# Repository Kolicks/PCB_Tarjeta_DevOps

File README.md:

# ⚙️ PCB_Tarjeta_DevOps
**Generic Development Console with Ethernet and USB Connectivity**

---

<p align="center">
  
</p>

---

## 📘 Overview
**PCB_Tarjeta_DevOps** is a versatile, custom-designed console PCB created primarily as a **personal exercise in complex two-layer design and Ethernet integration**.  
It serves as a **general-purpose development board** adapted from the **ST Nucleo-F412ZG** design, focusing on practical layout challenges and signal-integrity learning (Ethernet, differential pairs, impedance control).

<p align="center">

  <br>
  <em>3D renders of the PCB_Tarjeta_DevOps — Top and Bottom views</em>
</p>

---

## ⚙️ General Information
- A **general-purpose console**, not intended for a specific application.  
- Designed as a **learning exercise**, implementing many components on only **two layers** to increase design difficulty.  
- Served as an **introduction to Ethernet PCB layout**, including **differential pair routing** and **impedance control**.  
- Several schematic blocks were **adapted from the ST Nucleo-F412ZG** for familiarity and reference.  

<p align="center">
  
  <br>
  <em>Full schematic diagram of the PCB_Tarjeta_DevOps (KiCad 9)</em>
</p>

---

## 🔧 Characteristics
- Acts as a **multi-purpose development console**.  
- Supports **USB power and programming**.  
- Integrates **Ethernet connectivity** with differential pair routing and impedance matching.  
- Includes **8 Inputs and 8 Outputs**:  
  - **Outputs for industrial/power use** driven by **ITS4090QEPDXUMA1** — up to **1.5 A** each, suitable for **24 V industrial control**.  
  - **8 isolated outputs** using **TLP290-4** optocouplers (potential-free, up to 24 V).  
- Features a **hardware switch selector** to toggle between **programming** and **debugging** modes.  
- Includes a **real-time clock (RTC)** with **CR2032 battery backup**.  
- Provides **five tactile buttons** for user interaction with the display or user interface.  

<p align="center">
  
  <br>
  <em>Top layer routing and overall PCB layout (KiCad 9)</em>
</p>

---

## ⚠️ Design Notes
- **Display Section:**  
  - Multiple components in the display area require mechanical supports and connectors.  
  - Some footprints should be marked as **DNP (Do Not Populate)** and clearly specified for **DFM/DFA** purposes.  
- **Ethernet Interface:**  
  - Differential pairs are **impedance-matched to 100 Ω**, validated using **JLCPCB’s impedance calculator** and fabrication stack-up data.  
  - **USB traces** are not impedance-controlled in this revision (planned improvement).  
- **DFM Analysis (JLCPCB DFM tool):**  
  - Found **drilling overlaps** in display-related holes (mechanical supports and signals).  
  - **USB-C footprint issue:** plated hole size **0.60 mm, required >0.61 mm** tolerance.  
- **Silkscreen and Drill Issues:**  
  - Some silkscreen elements **collide with through holes** but remain legible.  
  - **Line width warnings** flagged for narrow silkscreen traces — minor fabrication risk, acceptable in prototype runs.  
- Overall design remains **manufacturable** and **functionally valid**, despite minor DFM flags.  

---

## 🧩 Repository Structure
PCB_Tarjeta_DevOps/

├── schematic/ # KiCad schematic files

├── pcb_layout/ # KiCad PCB layout files

├── gerbers/ # Gerber fabrication files

├── images/ # Rendered visuals (3D, SCH, PCB)

├── LICENSE # Hardware license (CERN-OHL-P v2.0)

└── README.md # Project documentation

---

## 📜 License
This hardware design is released under the **CERN Open Hardware License v2 – Permissive (CERN-OHL-P-2.0)**.  
You are free to use, modify, and distribute this design, provided that:
- The license is included with redistributions.
- Proper credit is given to the original author.

More info: https://cern-ohl.web.cern.ch/

---

## 👤 Author
**Project:** PCB_Tarjeta_DevOps  
**Author:** [Kolicks]  
**Toolchain:** KiCad 9  
**Version:** 9.0  

---

## 🧱 Future Improvements
- Redesign **USB differential pair** routing with impedance control.  
- Correct **DFM-related drilling and silkscreen** warnings.  
- Mark **DNP parts** for display connectors and update BOM.

---

⭐ *If you find this project useful or educational, please consider starring the repository and sharing feedback!*

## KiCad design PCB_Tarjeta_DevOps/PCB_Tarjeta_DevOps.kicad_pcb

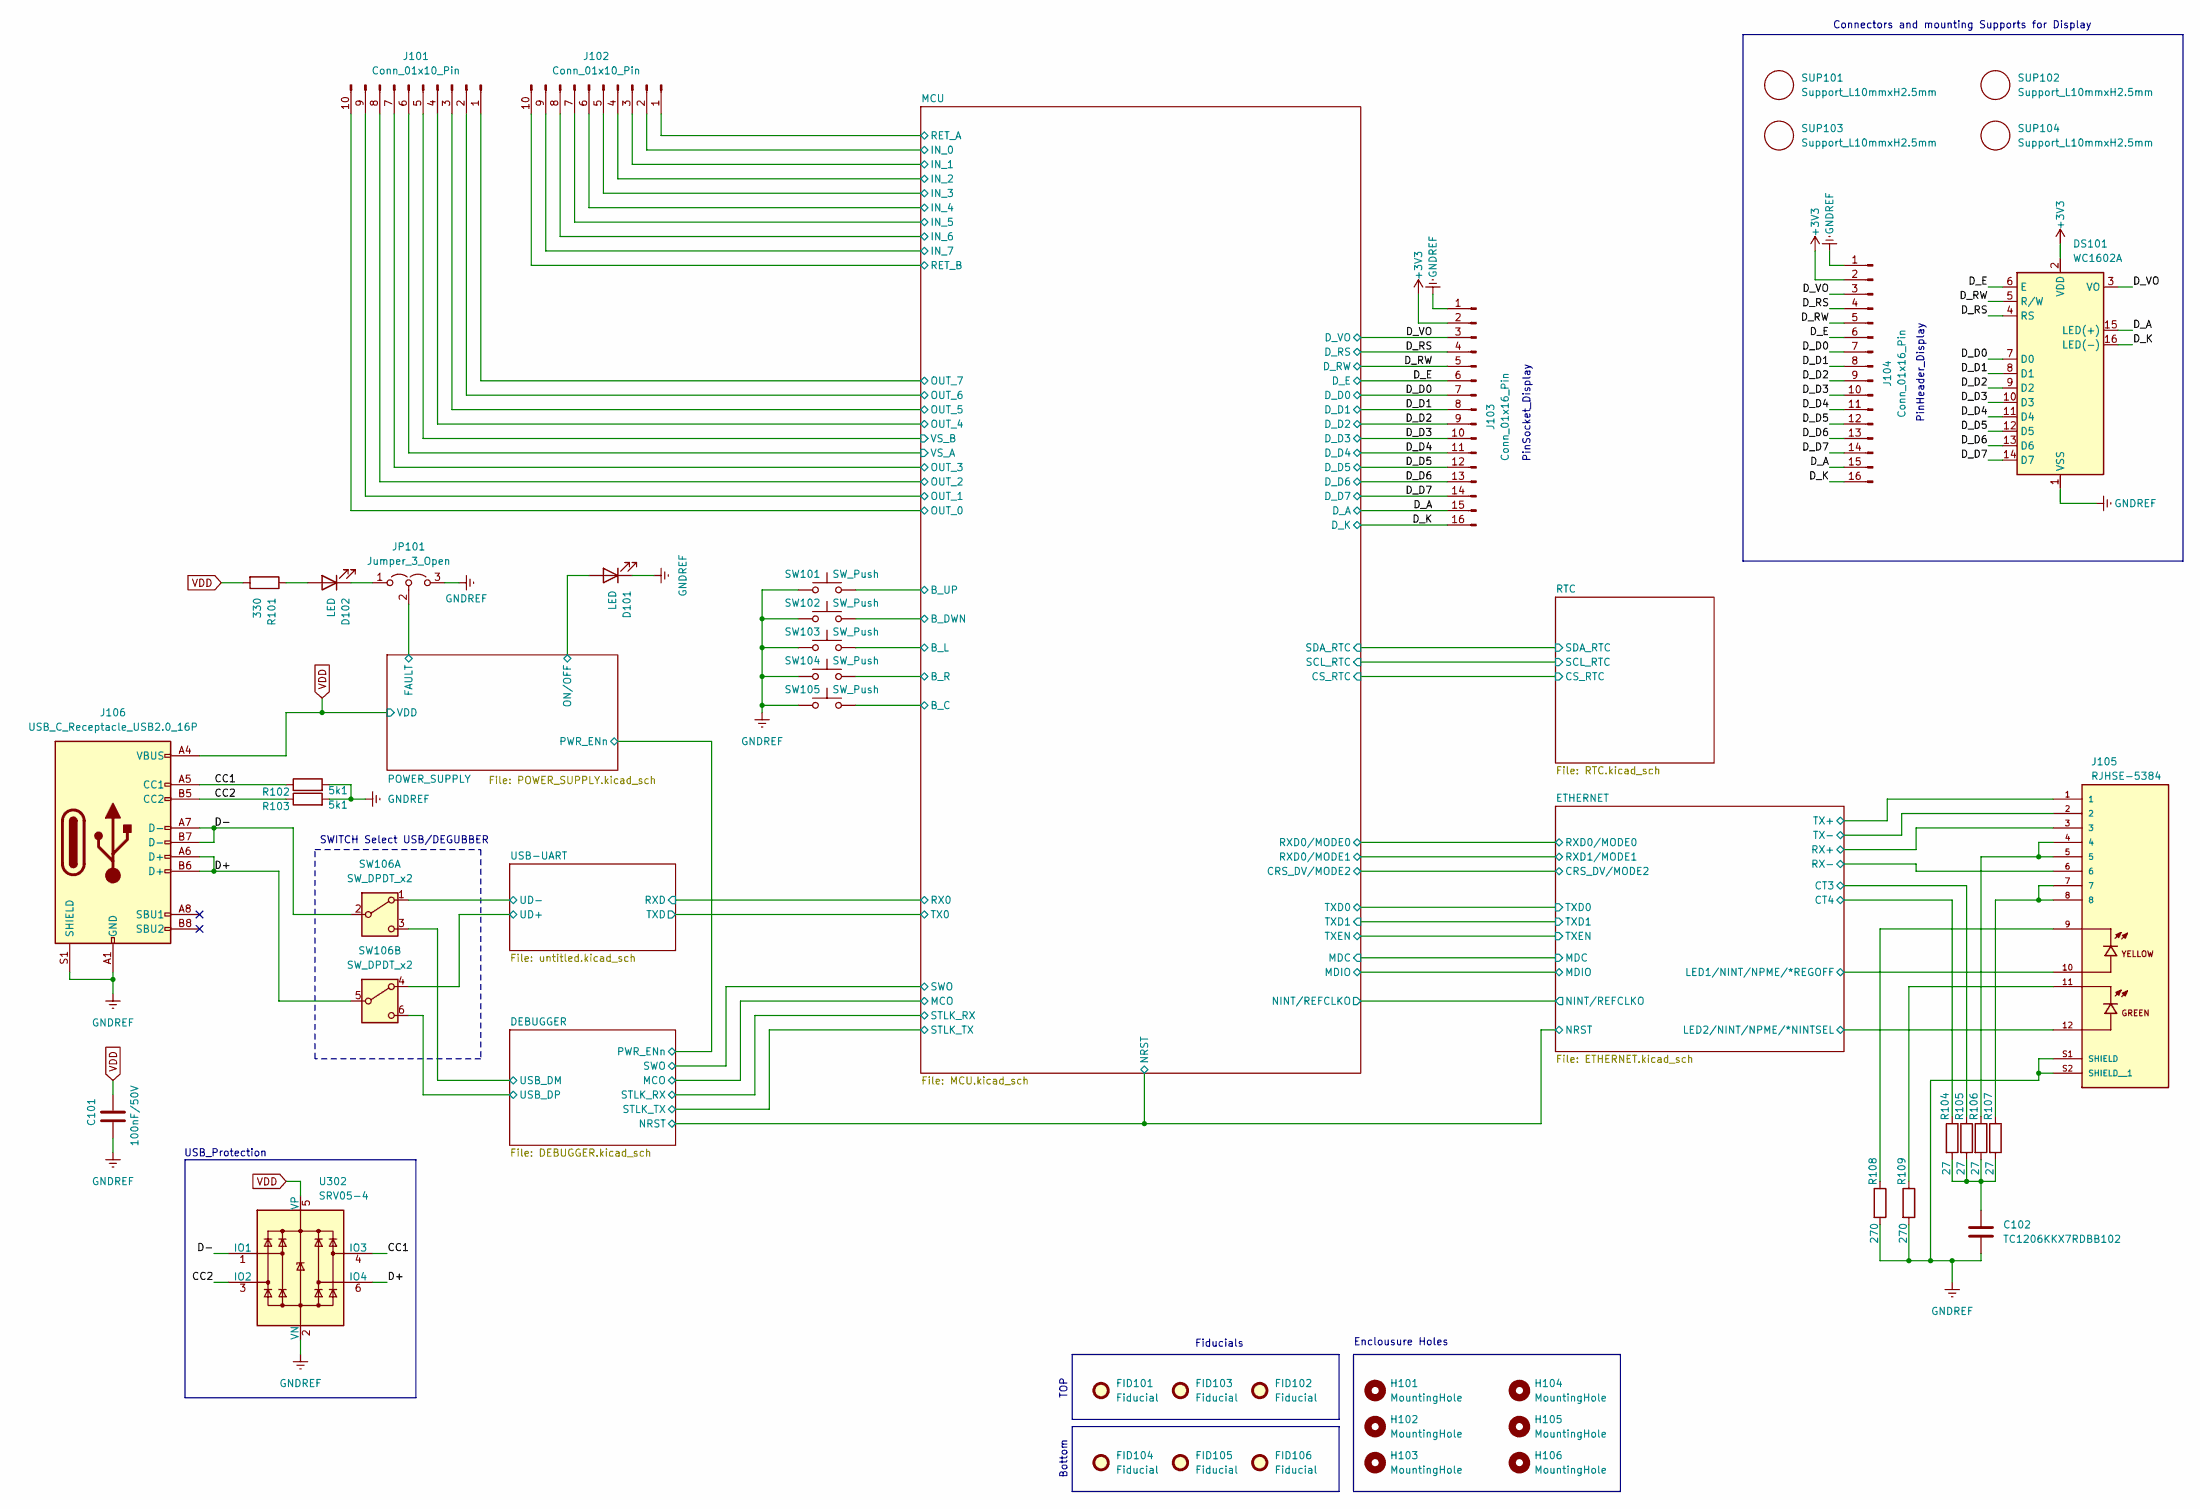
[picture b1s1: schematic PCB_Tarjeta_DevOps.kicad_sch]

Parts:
C101: 100nF/50V; C_0603_1608Metric_Pad1.08x0.95mm_HandSolder
C102: TC1206KKX7RDBB102; C_0603_1608Metric_Pad1.08x0.95mm_HandSolder
D101, D102: LED; LED_0201_0603Metric_Pad0.64x0.40mm_HandSolder
DS101: WC1602A
FID101, FID102, FID103, FID104, FID105, FID106: Fiducial; Fiducial_1.5mm_Mask3mm
H101, H102, H103, H104, H105, H106: MountingHole; MountingHole_3.2mm_M3_ISO14580
J101, J102: Conn_01x10_Pin; TerminalBlock_Phoenix_MPT-0,5-10-2.54_1x10_P2.54mm_Horizont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
J103: Conn_01x16_Pin; PinSocket_1x16_P2.54mm_Vertical
J104: Conn_01x16_Pin; PinHeader_1x16_P2.54mm_Vertical
J105: RJHSE-5384; AMPHENOL_RJHSE-5384; PARTREV E
J106: USB_C_Receptacle_USB2.0_16P; USB_C_Receptacle_Palconn_UTC16-G
JP101: Jumper_3_Open; PinHeader_1x03_P2.54mm_Vertical
R101: 330; R_0603_1608Metric_Pad0.98x0.95mm_HandSolder
R102, R103: 5k1; R_0603_1608Metric_Pad0.98x0.95mm_HandSolder
R104, R105, R106, R107: 27; R_0603_1608Metric_Pad0.98x0.95mm_HandSolder
R108, R109: 270; R_0603_1608Metric_Pad0.98x0.95mm_HandSolder
SUP101, SUP102, SUP103, SUP104: Support_L10mmxH2.5mm; Support_1x01_L1.0mmxH2.5mm_Vertical
SW101, SW102, SW103, SW104, SW105: SW_Push; SW_PUSH_6mm_H13mm
SW106: SW_DPDT_x2; SW_CK_JS202011CQN_DPDT_Straight
U302: SRV05-4; SOT-23-6

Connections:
+3V3: DS101.2 (VDD), J103.2, J104.2; also elsewhere on the board
/CC1: J106.A5 (CC1), R102.1, U302.4 (IO3)
/CC2: J106.B5 (CC2), R103.1, U302.3 (IO2)
/D+: J106.A6 (D+), J106.B6 (D+), SW106.5 (B), U302.6 (IO4)
/D-: J106.A7 (D-), J106.B7 (D-), SW106.2 (B), U302.1 (IO1)
/DEBUGGER/USB_DM: SW106.3 (C); also elsewhere on the board
/DEBUGGER/USB_DP: SW106.6 (C); also elsewhere on the board
/D_A: DS101.15 (LED(+)), J103.15, J104.15; also elsewhere on the board
/D_D0: DS101.7 (D0), J103.7, J104.7; also elsewhere on the board
/D_D1: DS101.8 (D1), J103.8, J104.8; also elsewhere on the board
/D_D2: DS101.9 (D2), J103.9, J104.9; also elsewhere on the board
/D_D3: DS101.10 (D3), J103.10, J104.10; also elsewhere on the board
/D_D4: DS101.11 (D4), J103.11, J104.11; also elsewhere on the board
/D_D5: DS101.12 (D5), J103.12, J104.12; also elsewhere on the board
/D_D6: DS101.13 (D6), J103.13, J104.13; also elsewhere on the board
/D_D7: DS101.14 (D7), J103.14, J104.14; also elsewhere on the board
/D_E: DS101.6 (E), J103.6, J104.6; also elsewhere on the board
/D_K: DS101.16 (LED(-)), J103.16, J104.16; also elsewhere on the board
/D_RS: DS101.4 (RS), J103.4, J104.4; also elsewhere on the board
/D_RW: DS101.5 (R/W), J103.5, J104.5; also elsewhere on the board
/D_VO: DS101.3 (VO), J103.3, J104.3; also elsewhere on the board
/ETHERNET/CT3: R105.1; also elsewhere on the board
/ETHERNET/CT4: R104.1; also elsewhere on the board
/ETHERNET/LED1/NINT/NPME/*REGOFF: J105.10; also elsewhere on the board
/ETHERNET/LED2/NINT/NPME/*NINTSEL: J105.12; also elsewhere on the board
/ETHERNET/RX+: J105.3; also elsewhere on the board
/ETHERNET/RX-: J105.6; also elsewhere on the board
/ETHERNET/TX+: J105.1; also elsewhere on the board
/ETHERNET/TX-: J105.2; also elsewhere on the board
/MCU/B_C: SW105.2; also elsewhere on the board
/MCU/B_DWN: SW102.2; also elsewhere on the board
/MCU/B_L: SW103.2; also elsewhere on the board
/MCU/B_R: SW104.2; also elsewhere on the board
/MCU/B_UP: SW101.2; also elsewhere on the board
/MCU/IN_0: J102.2; also elsewhere on the board
/MCU/IN_1: J102.3; also elsewhere on the board
/MCU/IN_2: J102.4; also elsewhere on the board
/MCU/IN_3: J102.5; also elsewhere on the board
/MCU/IN_4: J102.6; also elsewhere on the board
/MCU/IN_5: J102.7; also elsewhere on the board
/MCU/IN_6: J102.8; also elsewhere on the board
/MCU/IN_7: J102.9; also elsewhere on the board
/MCU/OUT_0: J101.10; also elsewhere on the board
/MCU/OUT_1: J101.9; also elsewhere on the board
/MCU/OUT_2: J101.8; also elsewhere on the board
/MCU/OUT_3: J101.7; also elsewhere on the board
/MCU/OUT_4: J101.4; also elsewhere on the board
/MCU/OUT_5: J101.3; also elsewhere on the board
/MCU/OUT_6: J101.2; also elsewhere on the board
/MCU/OUT_7: J101.1; also elsewhere on the board
/MCU/RET_A: J102.1; also elsewhere on the board
/MCU/RET_B: J102.10; also elsewhere on the board
/MCU/VS_A: J101.6; also elsewhere on the board
/MCU/VS_B: J101.5; also elsewhere on the board
/POWER_SUPPLY/FAULT: JP101.2 (C); also elsewhere on the board
/POWER_SUPPLY/ON/OFF: D101.2 (A); also elsewhere on the board
/USB-UART/UD+: SW106.4 (A); also elsewhere on the board
/USB-UART/UD-: SW106.1 (A); also elsewhere on the board
GNDREF: C101.2, C102.2, D101.1 (K), DS101.1 (VSS), J103.1, J104.1, J105.S1 (SHIELD), J105.S2 (SHIELD__1), J106.A1 (GND), J106.A12 (GND), J106.B1 (GND), J106.B12 (GND), J106.S1 (SHIELD), JP101.3 (B), R102.2, R103.2, R108.2, R109.2, SW101.1, SW102.1, SW103.1, SW104.1, SW105.1, U302.2 (VN); also elsewhere on the board
unnamed: C102.1, R104.2, R105.2, R106.2, R107.2
unnamed: D102.2 (A), R101.1
unnamed: D102.1 (K), JP101.1 (A)
unnamed: J105.4, J105.5, R106.1
unnamed: J105.7, J105.8, R107.1
unnamed: J105.9, R108.1
unnamed: J105.11, R109.1
VDD: C101.1, J106.A4 (VBUS), J106.A9 (VBUS), J106.B4 (VBUS), J106.B9 (VBUS), R101.2, U302.5 (VP); also elsewhere on the board

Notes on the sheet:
Bottom
PinHeader_Display
Connectors and mounting Supports for Display
USB_Protection
Enclousure Holes
Fiducials
SWITCH Select USB/DEGUBBER
TOP
PinSocket_Display

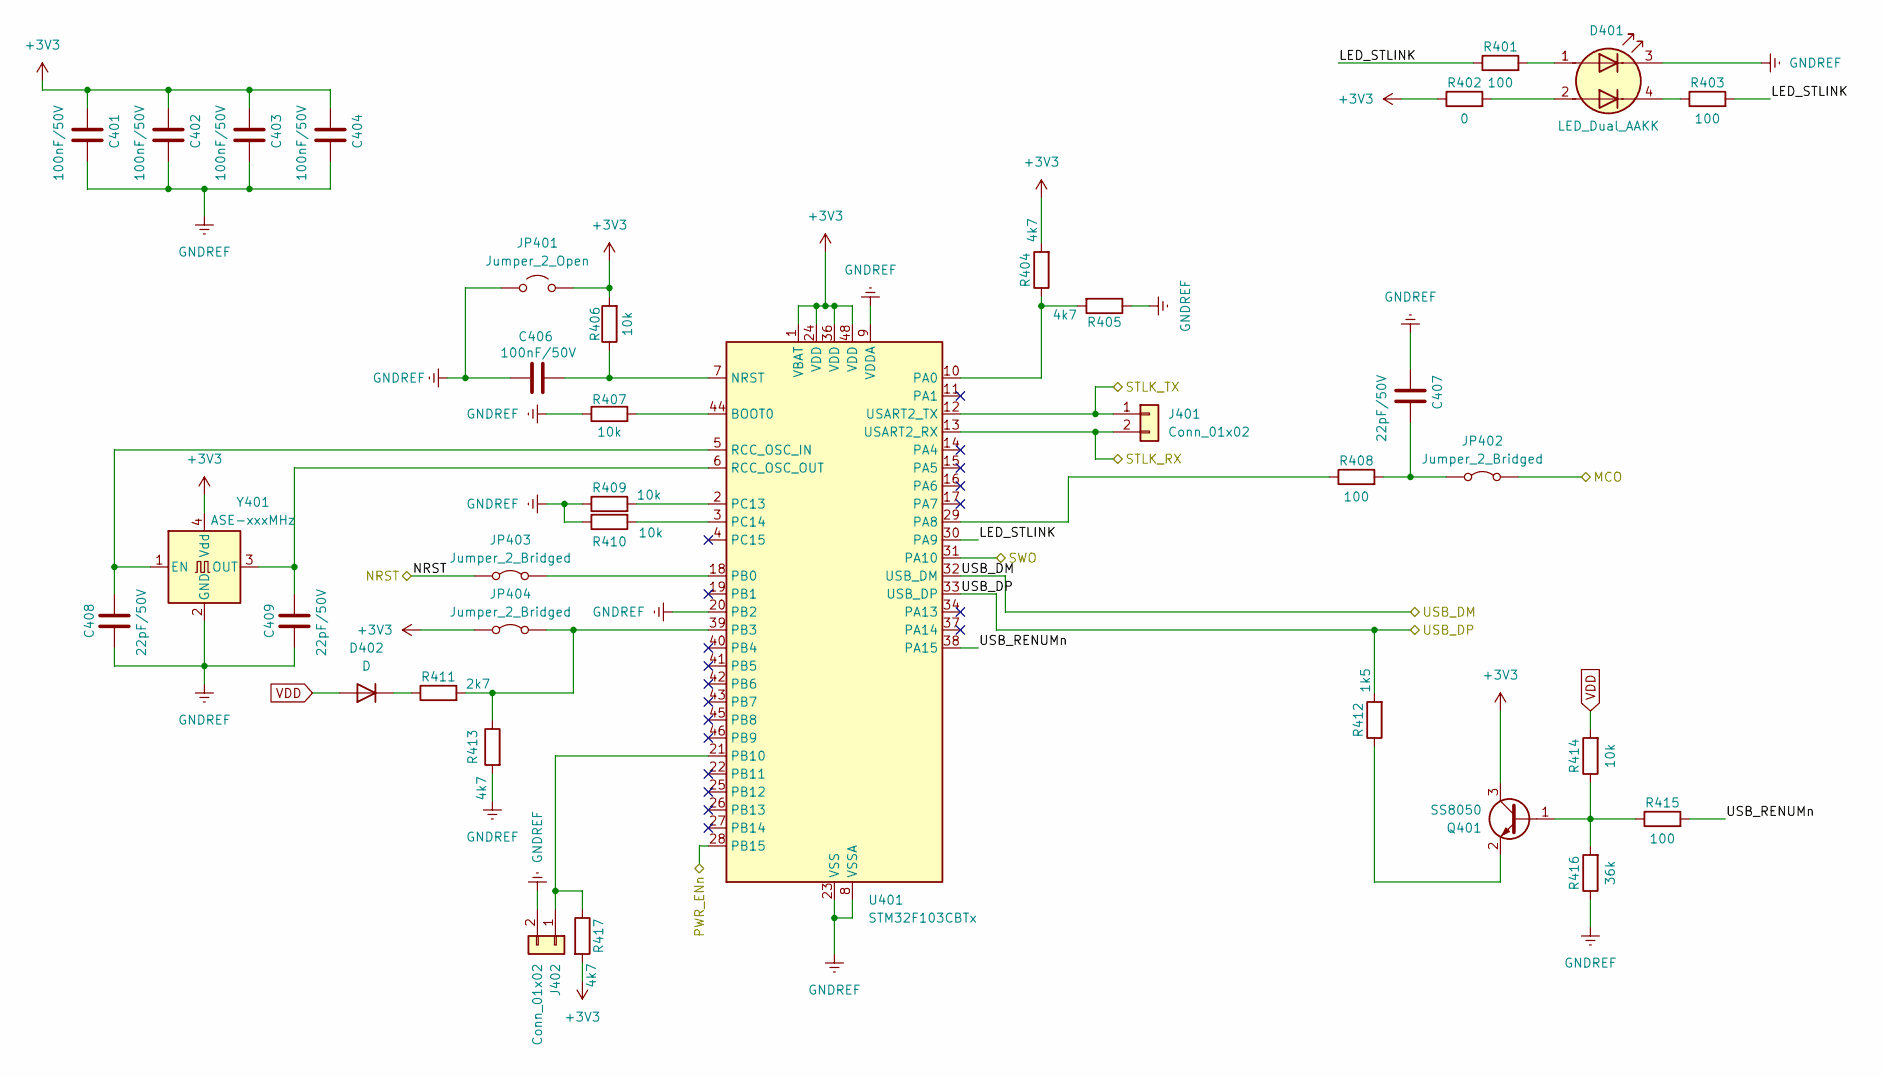
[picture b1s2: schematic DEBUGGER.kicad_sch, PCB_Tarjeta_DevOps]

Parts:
C401, C402, C403, C404, C406: 100nF/50V; C_0603_1608Metric_Pad1.08x0.95mm_HandSolder
C407, C408, C409: 22pF/50V; C_0603_1608Metric_Pad1.08x0.95mm_HandSolder
D401: LED_Dual_AAKK; LED_Inolux_IN-PI554FCH_PLCC4_5.0x5.0mm_P3.2mm
D402: D; D_SMA_Handsoldering
J401, J402: Conn_01x02; PinHeader_1x02_P2.54mm_Vertical
JP401: Jumper_2_Open; SolderJumper-2_P1.3mm_Open_TrianglePad1.0x1.5mm
JP402, JP403, JP404: Jumper_2_Bridged; SolderJumper-2_P1.3mm_Bridged_Pad1.0x1.5mm
Q401: SS8050; SOT-23W_Handsoldering
R401, R403, R408, R415: 100; R_0603_1608Metric_Pad0.98x0.95mm_HandSolder
R402: 0; R_0603_1608Metric_Pad0.98x0.95mm_HandSolder
R404, R405, R413, R417: 4k7; R_0603_1608Metric_Pad0.98x0.95mm_HandSolder
R406, R407, R409, R410, R414: 10k; R_0603_1608Metric_Pad0.98x0.95mm_HandSolder
R411: 2k7; R_0603_1608Metric_Pad0.98x0.95mm_HandSolder
R412: 1k5; R_0603_1608Metric_Pad0.98x0.95mm_HandSolder
R416: 36k; R_0603_1608Metric_Pad0.98x0.95mm_HandSolder
U401: STM32F103CBTx; LQFP-48_7x7mm_P0.5mm
Y401: ASE-xxxMHz; Oscillator_SMD_EuroQuartz_XO53-4Pin_5.0x3.2mm_HandSoldering

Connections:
+3V3: C401.1, C402.1, C403.1, C404.1, JP401.2 (B), JP404.1 (A), Q401.3 (C), R402.1, R404.2, R406.2, R417.2, U401.1 (VBAT), U401.24 (VDD), U401.36 (VDD), U401.48 (VDD), Y401.4 (Vdd); also elsewhere on the board
/DEBUGGER/LED_STLINK: R401.1, R403.2, U401.30 (PA9)
/DEBUGGER/MCO: JP402.2 (B); also elsewhere on the board
/DEBUGGER/NRST: JP403.1 (A); also elsewhere on the board
/DEBUGGER/PWR_ENn: U401.28 (PB15); also elsewhere on the board
/DEBUGGER/STLK_RX: J401.2, U401.13 (USART2_RX); also elsewhere on the board
/DEBUGGER/STLK_TX: J401.1, U401.12 (USART2_TX); also elsewhere on the board
/DEBUGGER/SWO: U401.31 (PA10); also elsewhere on the board
/DEBUGGER/USB_DM: U401.32 (USB_DM); also elsewhere on the board
/DEBUGGER/USB_DP: R412.2, U401.33 (USB_DP); also elsewhere on the board
/DEBUGGER/USB_RENUMn: R415.2, U401.38 (PA15)
GNDREF: C401.2, C402.2, C403.2, C404.2, C406.2, C407.1, C408.2, C409.2, D401.3 (K1), J402.2, JP401.1 (A), R405.1, R407.1, R409.1, R410.1, R413.2, R416.1, U401.8 (VSSA), U401.9 (VDDA), U401.20 (PB2), U401.23 (VSS), U401.35 (VSS), U401.47 (VSS), Y401.2 (GND); also elsewhere on the board
unnamed: D401.1 (A1), R401.2
unnamed: D401.2 (A2), R402.2
unnamed: D401.4 (K2), R403.1
unnamed: D402.1 (K), R411.1
unnamed: J402.1, R417.1, U401.21 (PB10)
unnamed: C407.2, JP402.1 (A), R408.2
unnamed: JP403.2 (B), U401.18 (PB0)
unnamed: JP404.2 (B), R411.2, R413.1, U401.39 (PB3)
unnamed: Q401.1 (B), R414.1, R415.1, R416.2
unnamed: Q401.2 (E), R412.1
unnamed: R407.2, U401.44 (BOOT0)
unnamed: C406.1, R406.1, U401.7 (NRST)
unnamed: R404.1, R405.2, U401.10 (PA0)
unnamed: R408.1, U401.29 (PA8)
unnamed: R409.2, U401.2 (PC13)
unnamed: R410.2, U401.3 (PC14)
unnamed: C408.1, U401.5 (RCC_OSC_IN), Y401.1 (EN)
unnamed: C409.1, U401.6 (RCC_OSC_OUT), Y401.3 (OUT)
VDD: D402.2 (A), R414.2; also elsewhere on the board

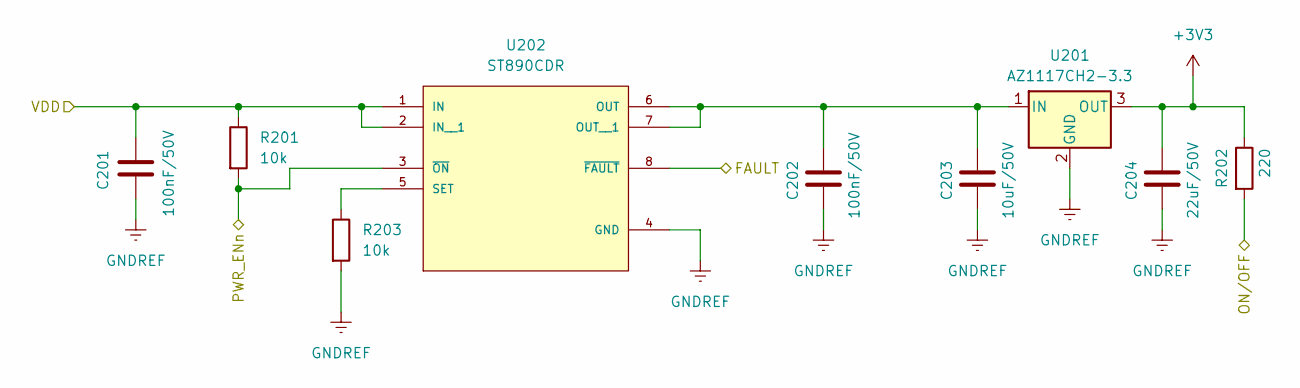
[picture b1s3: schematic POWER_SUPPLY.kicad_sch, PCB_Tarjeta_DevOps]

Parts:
C201, C202: 100nF/50V; C_0603_1608Metric_Pad1.08x0.95mm_HandSolder
C203: 10uF/50V; C_0603_1608Metric_Pad1.08x0.95mm_HandSolder
C204: 22uF/50V; C_0603_1608Metric_Pad1.08x0.95mm_HandSolder
R201, R203: 10k; R_0603_1608Metric_Pad0.98x0.95mm_HandSolder
R202: 220; R_0603_1608Metric_Pad0.98x0.95mm_HandSolder
U201: AZ1117CH2-3.3; TO-252-2
U202: ST890CDR; SOIC127P600X175-8N; PARTREV 10

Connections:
+3V3: C204.1, R202.1, U201.3 (OUT); also elsewhere on the board
/DEBUGGER/PWR_ENn: R201.2, U202.3 (~ON); also elsewhere on the board
/POWER_SUPPLY/FAULT: U202.8 (~FAULT); also elsewhere on the board
/POWER_SUPPLY/ON/OFF: R202.2; also elsewhere on the board
GNDREF: C201.2, C202.2, C203.2, C204.2, R203.2, U201.2 (GND), U202.4 (GND); also elsewhere on the board
unnamed: C202.1, C203.1, U201.1 (IN), U202.6 (OUT), U202.7 (OUT__1)
unnamed: R203.1, U202.5 (SET)
VDD: C201.1, R201.1, U202.1 (IN), U202.2 (IN__1); also elsewhere on the board

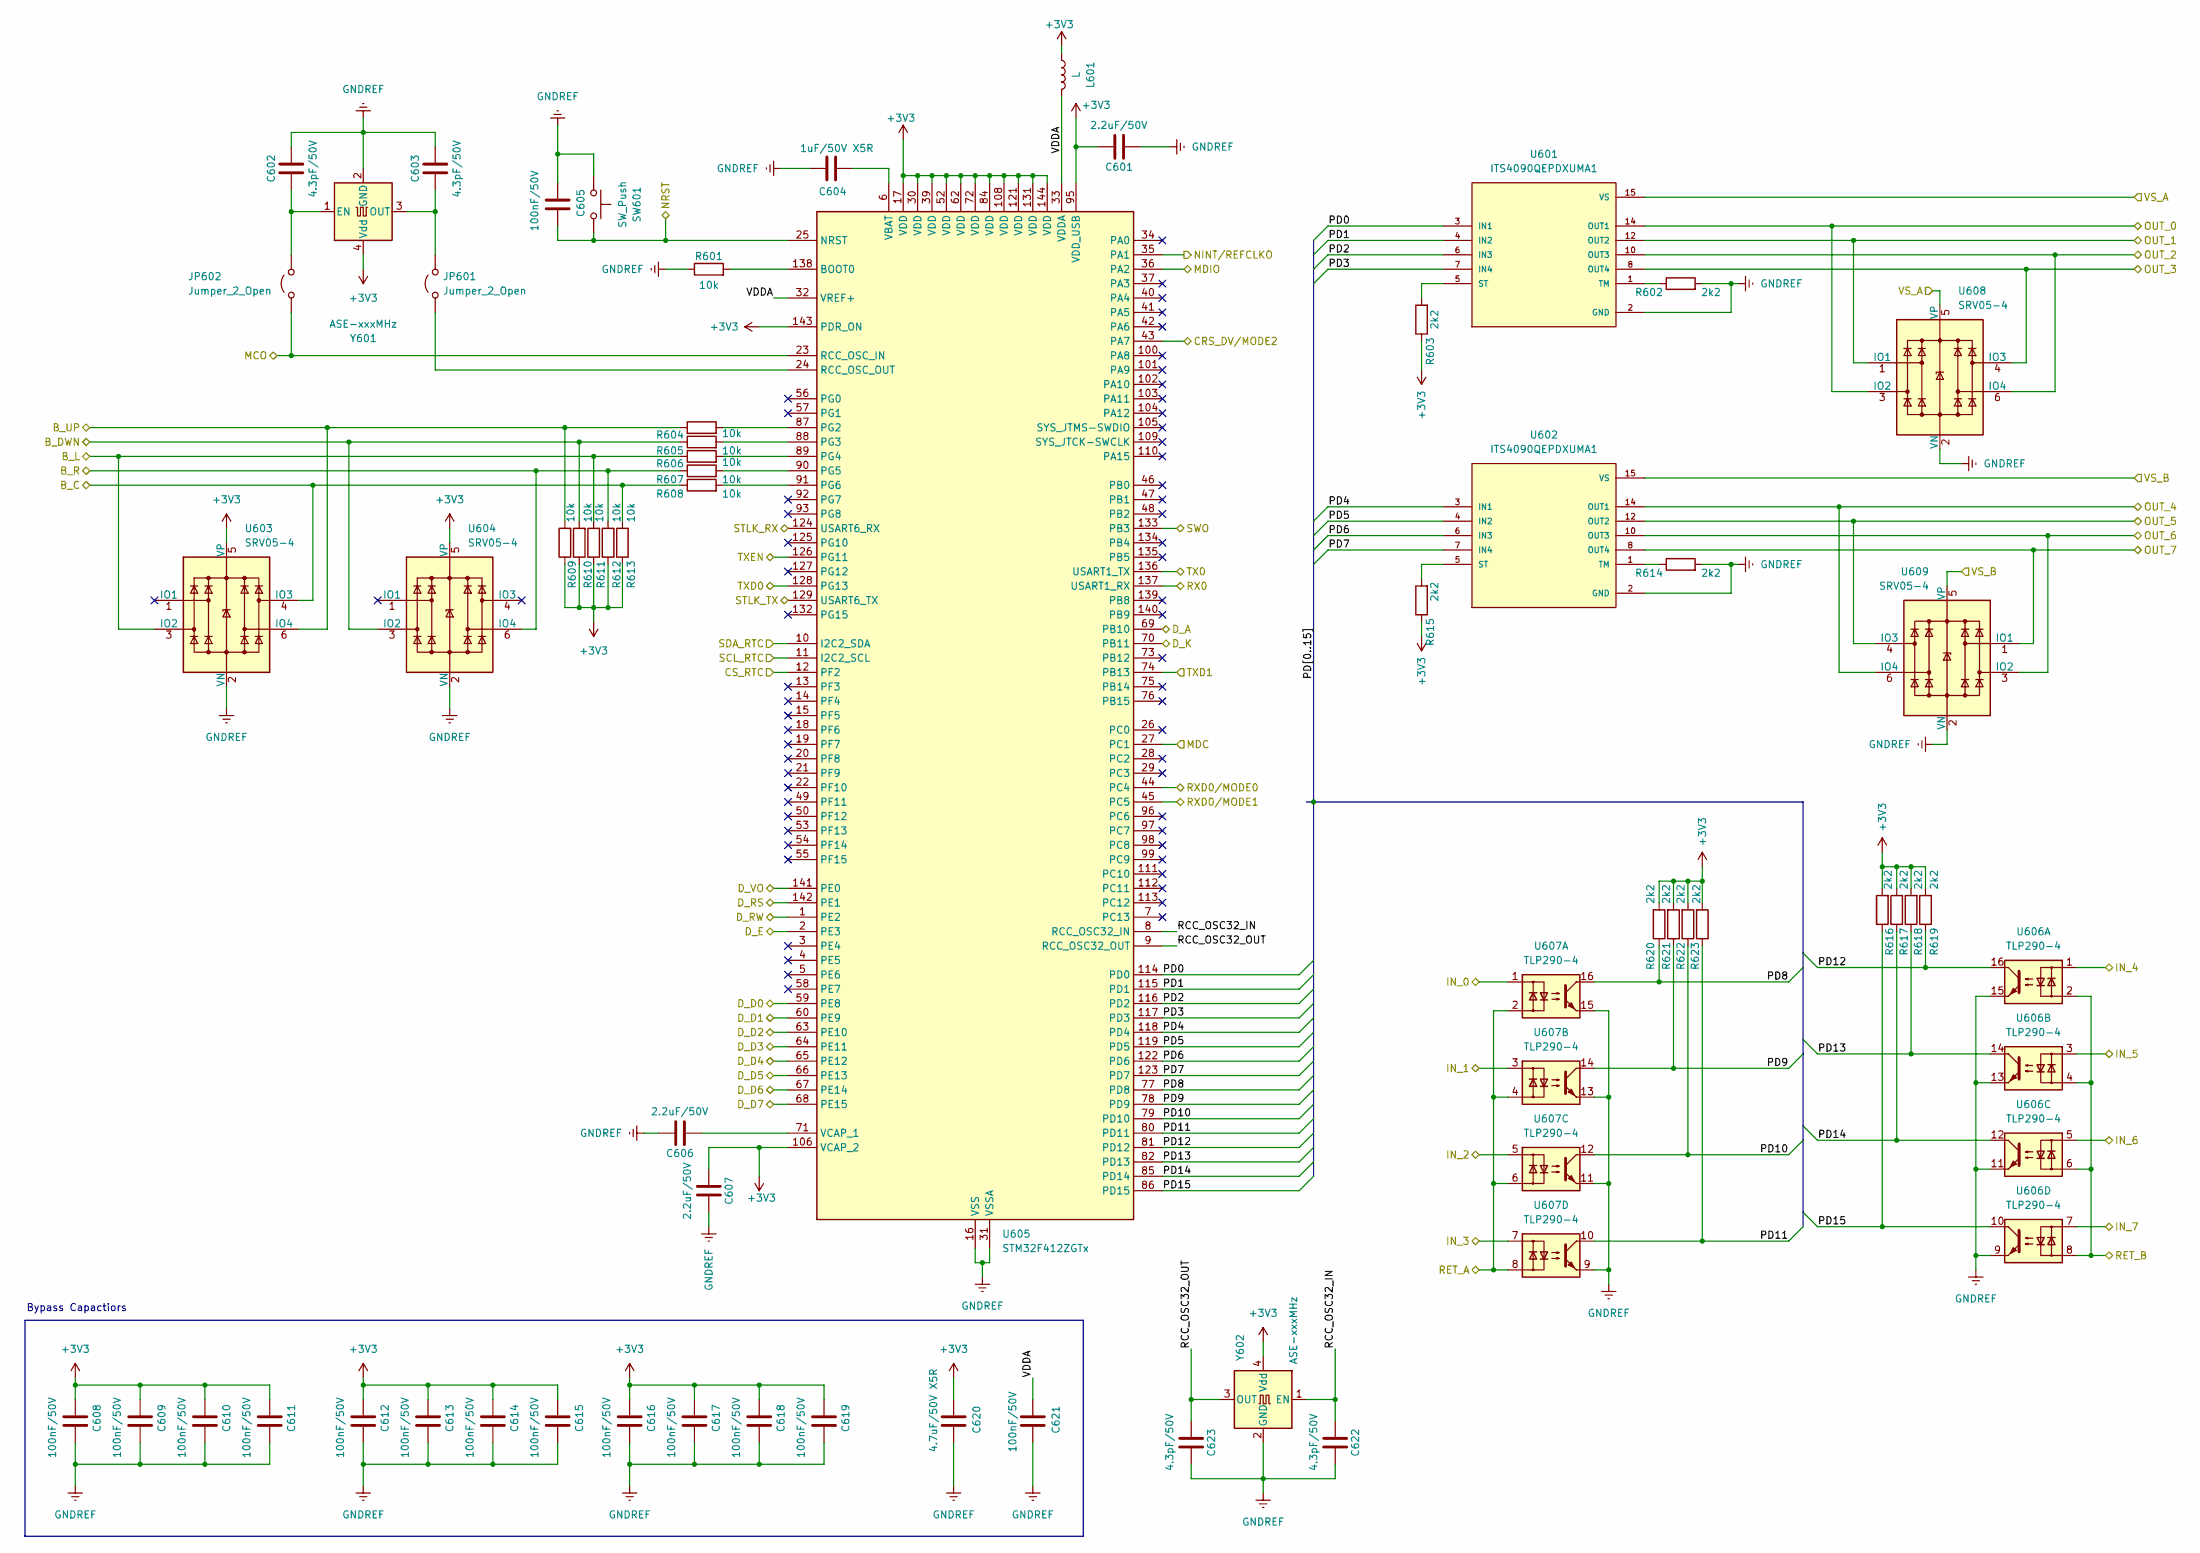
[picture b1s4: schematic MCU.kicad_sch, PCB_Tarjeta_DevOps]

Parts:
C601, C606, C607: 2.2uF/50V; C_0603_1608Metric_Pad1.08x0.95mm_HandSolder
C602, C603, C622, C623: 4.3pF/50V; C_0603_1608Metric_Pad1.08x0.95mm_HandSolder
C604: 1uF/50V X5R; C_0603_1608Metric_Pad1.08x0.95mm_HandSolder
C605, C608, C609, C610, C611, C612, C613, C614, C615, C616, C617, C618, C619, C621: 100nF/50V; C_0603_1608Metric_Pad1.08x0.95mm_HandSolder
C620: 4.7uF/50V X5R; C_0603_1608Metric_Pad1.08x0.95mm_HandSolder
JP601, JP602: Jumper_2_Open; SolderJumper-2_P1.3mm_Open_TrianglePad1.0x1.5mm
L601: L; L_0603_1608Metric_Pad1.05x0.95mm_HandSolder
R601, R604, R605, R606, R607, R608, R609, R610, R611, R612, R613: 10k; R_0603_1608Metric_Pad0.98x0.95mm_HandSolder
R602, R603, R614, R615, R616, R617, R618, R619, R620, R621, R622, R623: 2k2; R_0603_1608Metric_Pad0.98x0.95mm_HandSolder
SW601: SW_Push; SW_PUSH_6mm_H5mm
U601, U602: ITS4090QEPDXUMA1; SOP65P600X115-15N
U603, U604, U608, U609: SRV05-4; SOT-23-6
U605: STM32F412ZGTx; LQFP-144_20x20mm_P0.5mm
U606, U607: TLP290-4; SOP-16_4.4x10.4mm_P1.27mm
Y601, Y602: ASE-xxxMHz; Oscillator_SMD_EuroQuartz_XO53-4Pin_5.0x3.2mm_HandSoldering

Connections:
+3V3: C601.1, C607.2, C608.1, C609.1, C610.1, C611.1, C612.1, C613.1, C614.1, C615.1, C616.1, C617.1, C618.1, C619.1, C620.2, L601.1, R603.1, R609.1, R610.1, R611.1, R612.1, R613.1, R615.1, R616.2, R617.2, R618.2, R619.2, R620.2, R621.2, R622.2, R623.2, U603.5 (VP), U604.5 (VP), U605.17 (VDD), U605.30 (VDD), U605.39 (VDD), U605.52 (VDD), U605.62 (VDD), U605.72 (VDD), U605.84 (VDD), U605.95 (VDD_USB), U605.106 (VCAP_2), U605.108 (VDD), U605.121 (VDD), U605.131 (VDD), U605.143 (PDR_ON), U605.144 (VDD), Y601.4 (Vdd), Y602.4 (Vdd); also elsewhere on the board
/DEBUGGER/MCO: JP602.1 (A), U605.23 (RCC_OSC_IN); also elsewhere on the board
/DEBUGGER/NRST: C605.1, SW601.2, U605.25 (NRST); also elsewhere on the board
/DEBUGGER/STLK_RX: U605.124 (USART6_RX); also elsewhere on the board
/DEBUGGER/STLK_TX: U605.129 (USART6_TX); also elsewhere on the board
/DEBUGGER/SWO: U605.133 (PB3); also elsewhere on the board
/D_A: U605.69 (PB10); also elsewhere on the board
/D_D0: U605.59 (PE8); also elsewhere on the board
/D_D1: U605.60 (PE9); also elsewhere on the board
/D_D2: U605.63 (PE10); also elsewhere on the board
/D_D3: U605.64 (PE11); also elsewhere on the board
/D_D4: U605.65 (PE12); also elsewhere on the board
/D_D5: U605.66 (PE13); also elsewhere on the board
/D_D6: U605.67 (PE14); also elsewhere on the board
/D_D7: U605.68 (PE15); also elsewhere on the board
/D_E: U605.2 (PE3); also elsewhere on the board
/D_K: U605.70 (PB11); also elsewhere on the board
/D_RS: U605.142 (PE1); also elsewhere on the board
/D_RW: U605.1 (PE2); also elsewhere on the board
/D_VO: U605.141 (PE0); also elsewhere on the board
/ETHERNET/CRS_DV/MODE2: U605.43 (PA7); also elsewhere on the board
/ETHERNET/MDC: U605.27 (PC1); also elsewhere on the board
/ETHERNET/MDIO: U605.36 (PA2); also elsewhere on the board
/ETHERNET/NINT/REFCLKO: U605.35 (PA1); also elsewhere on the board
/ETHERNET/RXD0/MODE0: U605.44 (PC4); also elsewhere on the board
/ETHERNET/RXD1/MODE1: U605.45 (PC5); also elsewhere on the board
/ETHERNET/TXD0: U605.128 (PG13); also elsewhere on the board
/ETHERNET/TXD1: U605.74 (PB13); also elsewhere on the board
/ETHERNET/TXEN: U605.126 (PG11); also elsewhere on the board
/MCU/B_C: R608.1, R613.2, U603.4 (IO3); also elsewhere on the board
/MCU/B_DWN: R605.1, R610.2, U604.3 (IO2); also elsewhere on the board
/MCU/B_L: R606.1, R611.2, U603.3 (IO2); also elsewhere on the board
/MCU/B_R: R607.1, R612.2, U604.6 (IO4); also elsewhere on the board
/MCU/B_UP: R604.1, R609.2, U603.6 (IO4); also elsewhere on the board
/MCU/CS_RTC: U605.12 (PF2); also elsewhere on the board
/MCU/IN_0: U607.1; also elsewhere on the board
/MCU/IN_1: U607.3; also elsewhere on the board
/MCU/IN_2: U607.5; also elsewhere on the board
/MCU/IN_3: U607.7; also elsewhere on the board
/MCU/IN_4: U606.1; also elsewhere on the board
/MCU/IN_5: U606.3; also elsewhere on the board
/MCU/IN_6: U606.5; also elsewhere on the board
/MCU/IN_7: U606.7; also elsewhere on the board
/MCU/OUT_0: U601.14 (OUT1), U608.3 (IO2); also elsewhere on the board
/MCU/OUT_1: U601.12 (OUT2), U608.1 (IO1); also elsewhere on the board
/MCU/OUT_2: U601.10 (OUT3), U608.6 (IO4); also elsewhere on the board
/MCU/OUT_3: U601.8 (OUT4), U608.4 (IO3); also elsewhere on the board
/MCU/OUT_4: U602.14 (OUT1), U609.6 (IO4); also elsewhere on the board
/MCU/OUT_5: U602.12 (OUT2), U609.4 (IO3); also elsewhere on the board
/MCU/OUT_6: U602.10 (OUT3), U609.3 (IO2); also elsewhere on the board
/MCU/OUT_7: U602.8 (OUT4), U609.1 (IO1); also elsewhere on the board
/MCU/PD0: U601.3 (IN1), U605.114 (PD0)
/MCU/PD1: U601.4 (IN2), U605.115 (PD1)
/MCU/PD2: U601.6 (IN3), U605.116 (PD2)
/MCU/PD3: U601.7 (IN4), U605.117 (PD3)
/MCU/PD4: U602.3 (IN1), U605.118 (PD4)
/MCU/PD5: U602.4 (IN2), U605.119 (PD5)
/MCU/PD6: U602.6 (IN3), U605.122 (PD6)
/MCU/PD7: U602.7 (IN4), U605.123 (PD7)
/MCU/PD8: R620.1, U605.77 (PD8), U607.16
/MCU/PD9: R621.1, U605.78 (PD9), U607.14
/MCU/PD10: R622.1, U605.79 (PD10), U607.12
/MCU/PD11: R623.1, U605.80 (PD11), U607.10
/MCU/PD12: R619.1, U605.81 (PD12), U606.16
/MCU/PD13: R618.1, U605.82 (PD13), U606.14
/MCU/PD14: R617.1, U605.85 (PD14), U606.12
/MCU/PD15: R616.1, U605.86 (PD15), U606.10
/MCU/RCC_OSC32_IN: C622.1, U605.8 (RCC_OSC32_IN), Y602.1 (EN)
/MCU/RCC_OSC32_OUT: C623.1, U605.9 (RCC_OSC32_OUT), Y602.3 (OUT)
/MCU/RET_A: U607.2, U607.4, U607.6, U607.8; also elsewhere on the board
/MCU/RET_B: U606.2, U606.4, U606.6, U606.8; also elsewhere on the board
/MCU/RX0: U605.137 (USART1_RX); also elsewhere on the board
/MCU/SCL_RTC: U605.11 (I2C2_SCL); also elsewhere on the board
/MCU/SDA_RTC: U605.10 (I2C2_SDA); also elsewhere on the board
/MCU/TX0: U605.136 (USART1_TX); also elsewhere on the board
/MCU/VDDA: C621.2, L601.2, U605.32 (VREF+), U605.33 (VDDA)
/MCU/VS_A: U601.15 (VS), U608.5 (VP); also elsewhere on the board
/MCU/VS_B: U602.15 (VS), U609.5 (VP); also elsewhere on the board
GNDREF: C601.2, C602.2, C603.2, C604.1, C605.2, C606.1, C607.1, C608.2, C609.2, C610.2, C611.2, C612.2, C613.2, C614.2, C615.2, C616.2, C617.2, C618.2, C619.2, C620.1, C621.1, C622.2, C623.2, R601.1, R602.2, R614.2, SW601.1, U601.2 (GND), U602.2 (GND), U603.2 (VN), U604.2 (VN), U605.16 (VSS), U605.31 (VSSA), U605.38 (VSS), U605.51 (VSS), U605.61 (VSS), U605.83 (VSS), U605.94 (VSS), U605.107 (VSS), U605.120 (VSS), U605.130 (VSS), U606.9, U606.11, U606.13, U606.15, U607.9, U607.11, U607.13, U607.15, U608.2 (VN), U609.2 (VN), Y601.2 (GND), Y602.2 (GND); also elsewhere on the board
unnamed: JP601.1 (A), U605.24 (RCC_OSC_OUT)
unnamed: C603.1, JP601.2 (B), Y601.3 (OUT)
unnamed: C602.1, JP602.2 (B), Y601.1 (EN)
unnamed: R603.2, U601.5 (ST)
unnamed: R602.1, U601.1 (TM)
unnamed: R615.2, U602.5 (ST)
unnamed: R614.1, U602.1 (TM)
unnamed: R601.2, U605.138 (BOOT0)
unnamed: R604.2, U605.87 (PG2)
unnamed: R605.2, U605.88 (PG3)
unnamed: R606.2, U605.89 (PG4)
unnamed: R607.2, U605.90 (PG5)
unnamed: R608.2, U605.91 (PG6)
unnamed: C604.2, U605.6 (VBAT)
unnamed: C606.2, U605.71 (VCAP_1)

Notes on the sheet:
Bypass Capactiors
